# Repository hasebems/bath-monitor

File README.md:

# bath-monitor

5人家族の我が家では、お風呂に最後に入った人が湯船の水を抜いて洗うことになっています。しかし、その運用には以下の問題があります。
- まだ入ってない人がいるのに、湯船が空になって洗われていた
- もうみんな入ったのに、まだ入っていない人がいると勘違いして、そのまま朝まで湯船が洗われなかった

その後、入った人は磁石で印を付けるようにしたのですが、その運用は徹底されず、たびたびお風呂に関する問題が起き続けています。  

この bath-monitor はそんな家族の問題を解決するために開発しました。  
bath-monitor は以下の機能を持っています。
- 家族ごとに５つのボタンを搭載。ボタンが押されると LED が点灯し、ボタンごとに異なるメロディを鳴らす
- ボタンの押し間違いがあったら、二秒の長押しで LED は消灯し、キャンセルできる
- 照度センサーを搭載し、脱衣所が明るいか暗いかで誰かが入っていることをセンシングする
- ボタンとセンサーの信号はWi-Fi経由で自宅LAN上のFlaskサーバーに送られ、サーバーはライブダッシュボードを表示
- 携帯や PC でダッシュボードにアクセスすれば、誰が入ったか、今誰かが入っているかをリアルタイムに検知可能

設計の詳細は`docs/design.md`、HTTPの契約(プロトコル)は`docs/protocol.md`、ピン割り当ては`docs/wiring.md`を参照してください。embassy-rpのPIOの不具合の調査記録と回避策は`docs/embassy-rp-pio-drop-bug.md`にまとめています。

また、筐体や電子回路の作り方については、fabble の方にまとめました。  
https://fabble.cc/kigakudoh/bathmonitor

## サーバー

```bash
cd server
python -m venv .venv && source .venv/bin/activate
pip install -r requirements.txt
python app.py            # 開発用サーバー(手元での確認用。警告が出るのは正常) http://<this-machine>:8080
python wsgi.py           # 本番用サーバー(waitress。Pi上ではこちら) 同じく :8080
```

テスト: `pytest tests/ -q`(`server/`ディレクトリで、venvを有効化した状態で実行)。

Raspberry Pi上でsystemdサービスとして24時間365日稼働させる方法(`wsgi.py`経由の本番用WSGIサーバー、自動起動・自動再起動)は`docs/deploy.md`を参照してください。

## ファームウェア

`rustup target add thumbv8m.main-none-eabihf`(RP2350はArm Cortex-M33のため)と、書き込み用に`picotool`をPATHに通しておく必要があります(デバッグプローブ不要 — 書き込みはBOOTSEL + `picotool`で行います。`elf2uf2-rs`はRP2350/RP235xでは動作しません)。

```bash
cp firmware/src/secrets.rs.example firmware/src/secrets.rs   # 実際のWi-Fi/サーバー情報を記入
cd firmware
cargo build --release     # コンパイルチェックのみ
cargo run --release       # ビルドし、BOOTSELモードのPico 2 Wにpicotool経由で書き込み
```

ログはUSBシリアル経由(`screen /dev/tty.usbmodemXXXX 115200`)で確認します(RTT/defmtではありません)。

- `XXXX`の部分: Pico 2 WをUSB接続した状態で`ls /dev/tty.usbmodem*`を実行すると確認できる(複数のUSBシリアルデバイスが繋がっている場合は、抜き差し前後で`ls`の差分を見ると確実)
- `screen`の終了方法: `Ctrl-a`の後に`k`を押し、確認プロンプトで`y`を押す(`Ctrl-a` `d`はデタッチのみでプロセスは残るため注意)

## 現在の状況

- 専用の基板が届き、試作機を1台組み立てて動作検証を行いました。2026-10-11から我が家で運用を開始しています
- サーバーは実機のRaspberry Pi 4上にデプロイ・動作確認済み(ダッシュボードに自宅LAN上のスマートフォンからアクセスできることを確認済み)
- 対象基板は Pico W から Pico 2 W(RP2350) に変更となり、ファームウェアのコードはRP2350向けに移行済みです(`thumbv8m.main-none-eabihf`向けに`cargo clippy`まで通過)
- その後2026-09-19に実機のPico 2 Wへ書き込み、Wi-Fi接続、ボタン(1個目)、MAX98357Aアンプからのメロディ、オンボードLED、サーバーへの送信は動作を確認済み
- 照度センサーは、センサーを覆うとデバウンスされた在室状態が`POST /api/occupancy`で送られ、サーバーのダッシュボードにも在室と表示されることを確認済みです(2026-09-20)
- NeoPixelは、点灯・白の呼吸・長押し取り消しでの消灯を確認済みです(白の呼吸は、SK6812RGBWを5個つないで、1秒周期の現在の見え方で確認。点灯と長押し取り消しはWS2812の時に確認)。
- ここまではブレッドボード上での確認です。基板で組んだ試作機では、さらに次の項目を確認しました(2026-10-11): 5個すべてのボタンと押した人ごとの色、最後の1人の専用メロディ、音量・音割れ、Wi-Fi切断後の再接続、オフライン中・サーバー停止中の押下/取り消しの再送、接続失敗時のオンボードLEDの「ピピ」
- 照度センサーのしきい値(トリムポット)を夜の脱衣所の明るさに合わせて調整しましたが、昼間は人がいなくてかなり暗い状態でも、在室と判断されてしまいます

### 今後の検討事項

実運用を続けながら検討します(詳細は`docs/additional_spec.md`)。

- 照度センサーによる在室判定を、時刻(昼か夜か)と組み合わせて行う
- 人が入っていないときは、NeoPixelをかなり暗くするか、完全に消す

### 報告記録

- Fablab浜松の定例会合にて
- CoderDojo浜松の発表
    - 2026/9/27 (`docs/slides/bath-monitor-intro.pptx`)
    - 2026/10/25

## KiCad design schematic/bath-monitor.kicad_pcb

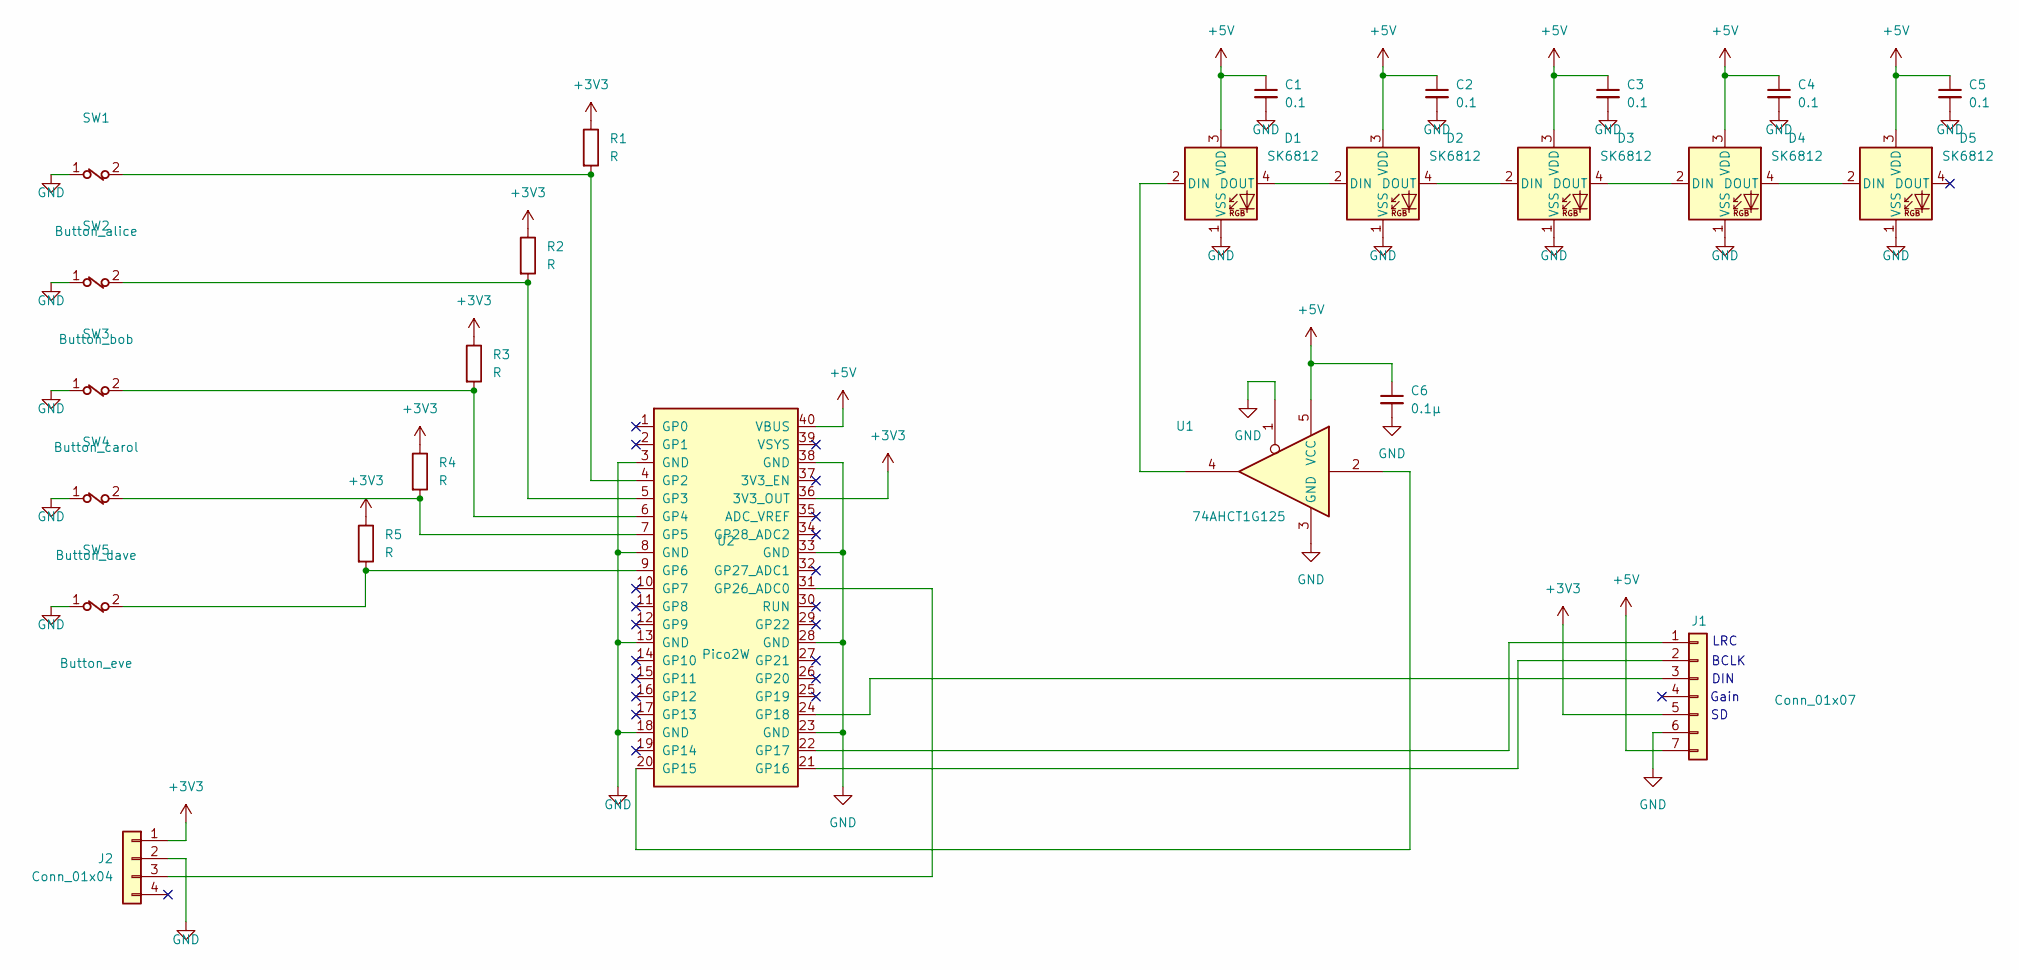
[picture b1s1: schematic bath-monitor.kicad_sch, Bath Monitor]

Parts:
C1, C2, C3, C4, C5: 0.1; C_Disc_D3.0mm_W1.6mm_P2.50mm
C6: 0.1μ; C_Disc_D3.0mm_W1.6mm_P2.50mm
D1, D2, D3, D4, D5: SK6812; LED_SK6812_PLCC4_5.0x5.0mm_P3.2mm
J1: Conn_01x07; PinHeader_1x07_P2.54mm_Vertical
J2: Conn_01x04; PinHeader_1x04_P2.54mm_Vertical
R1, R2, R3, R4, R5: R; R_Axial_DIN0207_L6.3mm_D2.5mm_P10.16mm_Horizontal
SW1: Button_alice; SW_PUSH-12mm
SW2: Button_bob; SW_PUSH-12mm
SW3: Button_carol; SW_PUSH-12mm
SW4: Button_dave; SW_PUSH-12mm
SW5: Button_eve; SW_PUSH-12mm
U1: 74AHCT1G125; SOT-23-5_HandSoldering
U2: Pico2W; RaspberryPi_Pico_Common_THT

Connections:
+3V3: J1.5, J2.1, R1.1, R2.1, R3.1, R4.1, R5.1, U2.36 (3V3_OUT)
+5V: C1.1, C2.1, C3.1, C4.1, C5.1, C6.1, D1.3 (VDD), D2.3 (VDD), D3.3 (VDD), D4.3 (VDD), D5.3 (VDD), J1.7, U1.5 (VCC), U2.40 (VBUS)
GND: C1.2, C2.2, C3.2, C4.2, C5.2, C6.2, D1.1 (VSS), D2.1 (VSS), D3.1 (VSS), D4.1 (VSS), D5.1 (VSS), J1.6, J2.2, SW1.1, SW2.1, SW3.1, SW4.1, SW5.1, U1.1, U1.3 (GND), U2.3 (GND), U2.8 (GND), U2.13 (GND), U2.18 (GND), U2.23 (GND), U2.28 (GND), U2.33 (GND), U2.38 (GND)
unnamed: D1.2 (DIN), U1.4
unnamed: D1.4 (DOUT), D2.2 (DIN)
unnamed: D2.4 (DOUT), D3.2 (DIN)
unnamed: D3.4 (DOUT), D4.2 (DIN)
unnamed: D4.4 (DOUT), D5.2 (DIN)
unnamed: J1.1, U2.22 (GP17)
unnamed: J1.2, U2.21 (GP16)
unnamed: J1.3, U2.24 (GP18)
unnamed: J2.3, U2.31 (GP26_ADC0)
unnamed: R1.2, SW1.2, U2.4 (GP2)
unnamed: R2.2, SW2.2, U2.5 (GP3)
unnamed: R3.2, SW3.2, U2.6 (GP4)
unnamed: R4.2, SW4.2, U2.7 (GP5)
unnamed: R5.2, SW5.2, U2.9 (GP6)
unnamed: U1.2, U2.20 (GP15)

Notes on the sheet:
Gain
DIN
LRC
BCLK

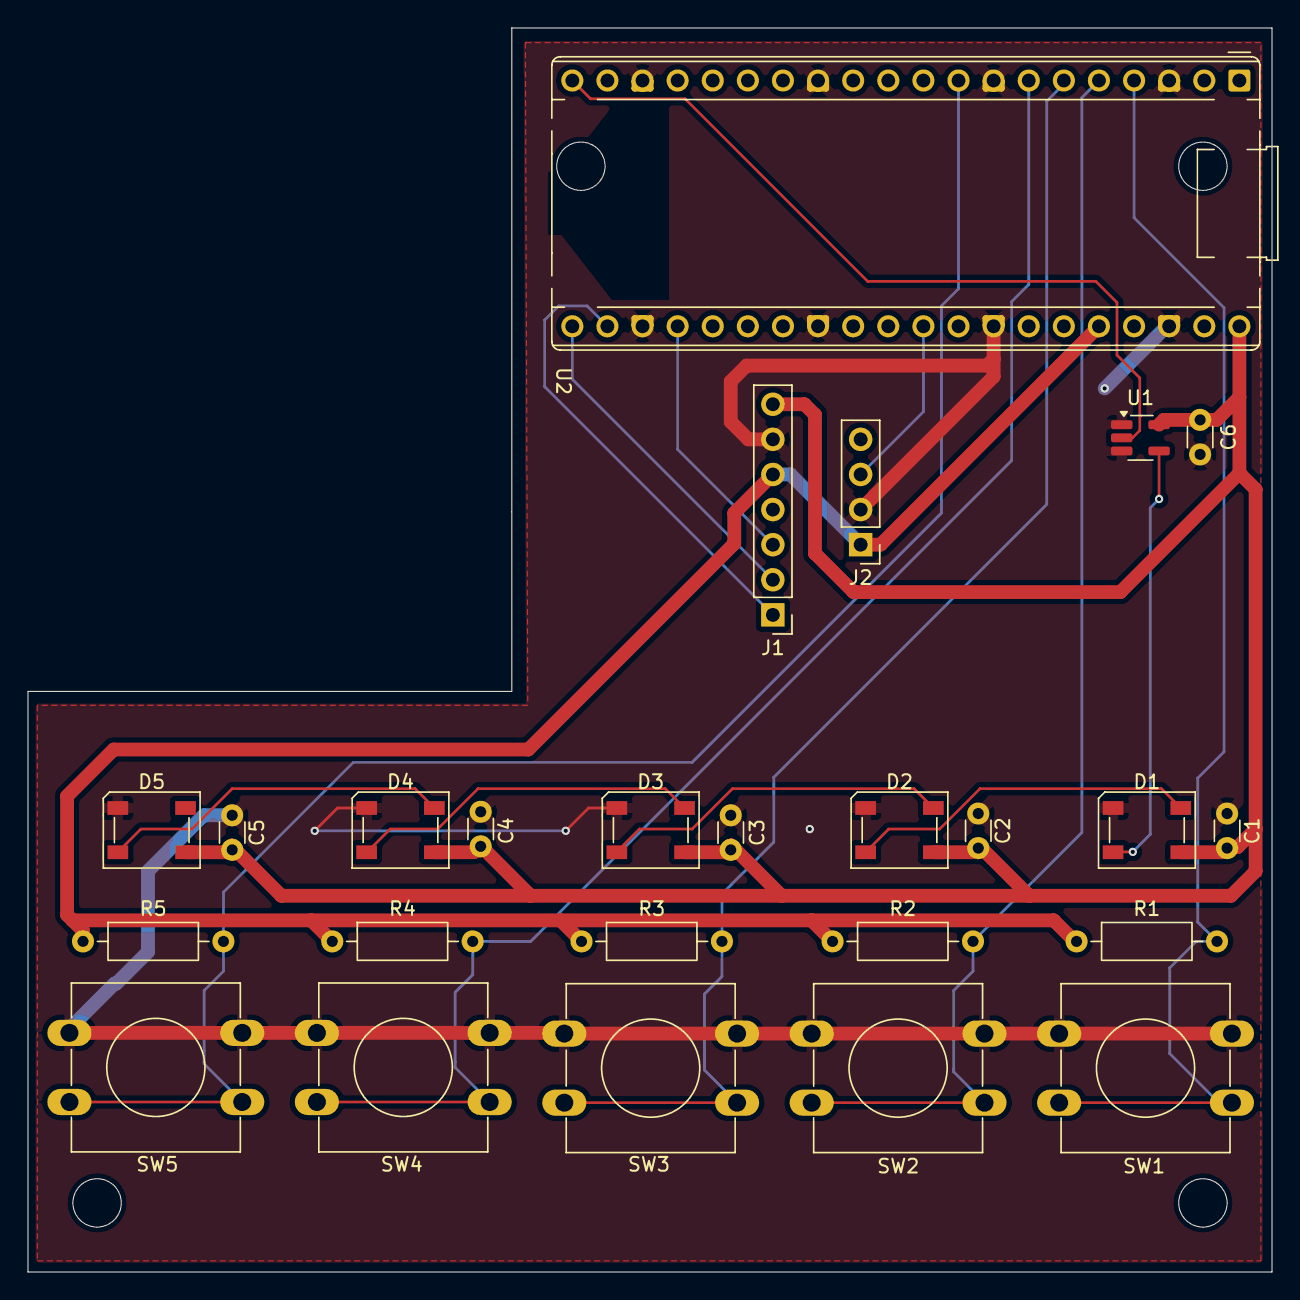
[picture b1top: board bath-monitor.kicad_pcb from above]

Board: 2 copper layers, 90.0 x 90.0 mm, 25 parts (0 on the bottom side), 18 nets.
